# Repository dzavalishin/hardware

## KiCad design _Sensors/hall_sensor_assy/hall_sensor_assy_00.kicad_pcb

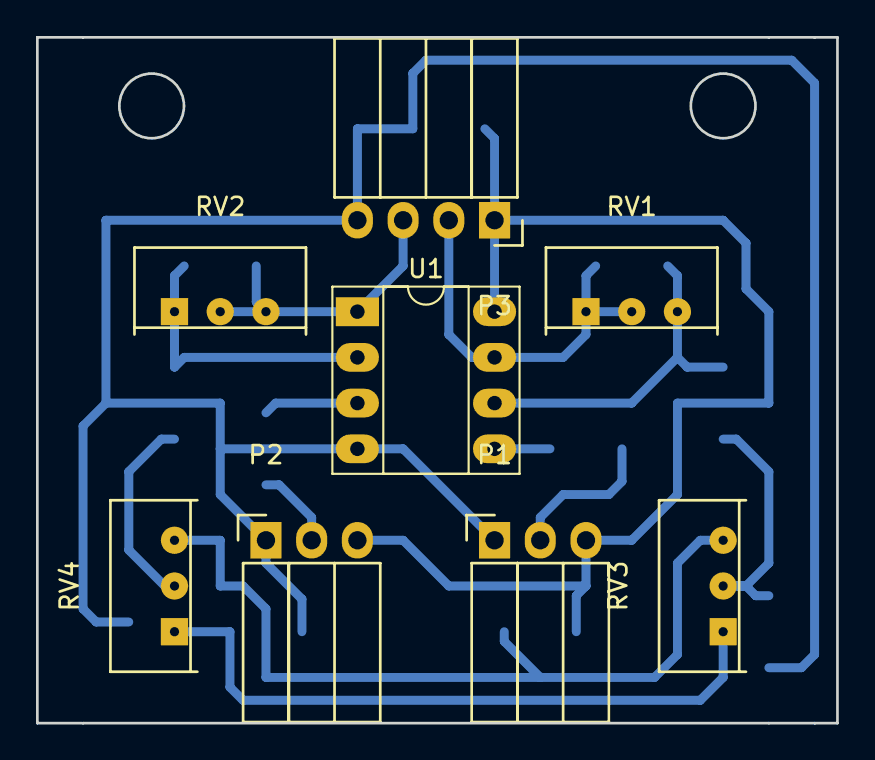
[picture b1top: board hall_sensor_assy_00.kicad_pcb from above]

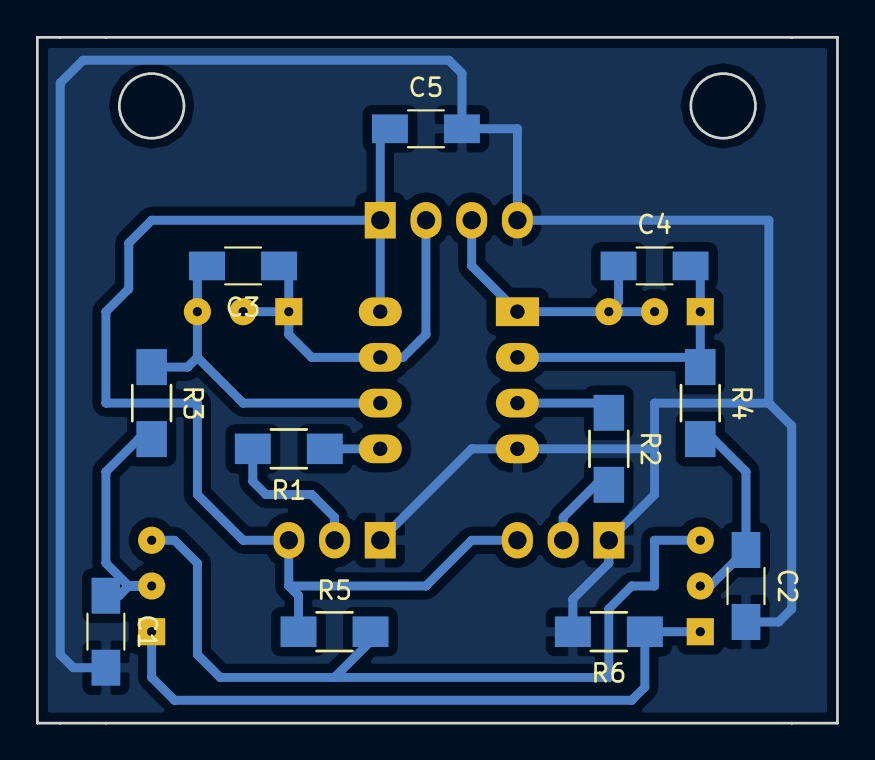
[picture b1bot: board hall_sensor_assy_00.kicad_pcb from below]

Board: 2 copper layers, 44.5 x 38.1 mm, 19 parts (11 on the bottom side), 14 nets.

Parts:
C1, C2, C5: 0,1; C_1206_HandSoldering
C3, C4: 0,01; C_1206_HandSoldering
P1: Hall_L; Socket_Strip_Angled_1x03
P2: Hall_R; Socket_Strip_Angled_1x03
P3: CONN_01X04; Socket_Strip_Angled_1x04
R1, R2: 10k; R_1206_HandSoldering
R3, R4: 22k; R_1206_HandSoldering
R5, R6: 1k; R_1206_HandSoldering
RV1, RV2: 22k; Potentiometer_Trimmer-Suntan-TSR-3386C
RV3, RV4: 2,2k; Potentiometer_Trimmer-Suntan-TSR-3386C
U1: MCP602; DIP-8_W7.62mm_Socket_LongPads

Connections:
+5V: C5.1, P1.3, P2.3, P3.1, R5.1, U1.8
GND: C1.2, C2.2, C5.2, P1.1, P2.1, P3.4, R6.2, U1.4
unnamed: C1.1, R3.2, RV3.2
unnamed: C2.1, R4.2, RV4.2
unnamed: C3.1, P3.2, RV1.1, RV1.2, U1.7
unnamed: C3.2, R3.1, RV1.3, U1.6
unnamed: C4.1, P3.3, RV2.2, RV2.3, U1.1
unnamed: C4.2, R4.1, RV2.1, U1.2
unnamed: P1.2, R1.2
unnamed: P2.2, R2.2
unnamed: R1.1, U1.5
unnamed: R2.1, U1.3
unnamed: R5.2, RV3.3, RV4.3
unnamed: R6.1, RV3.1, RV4.1

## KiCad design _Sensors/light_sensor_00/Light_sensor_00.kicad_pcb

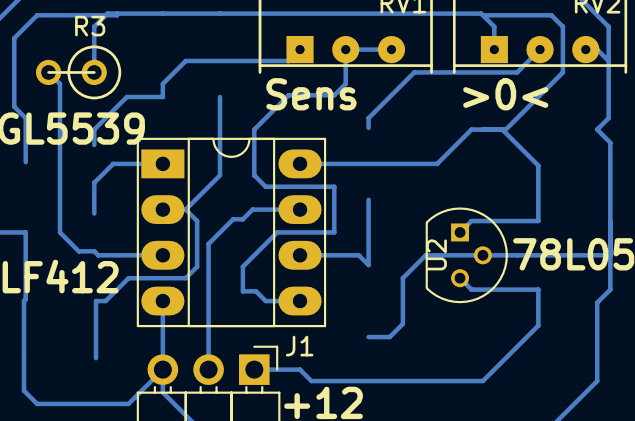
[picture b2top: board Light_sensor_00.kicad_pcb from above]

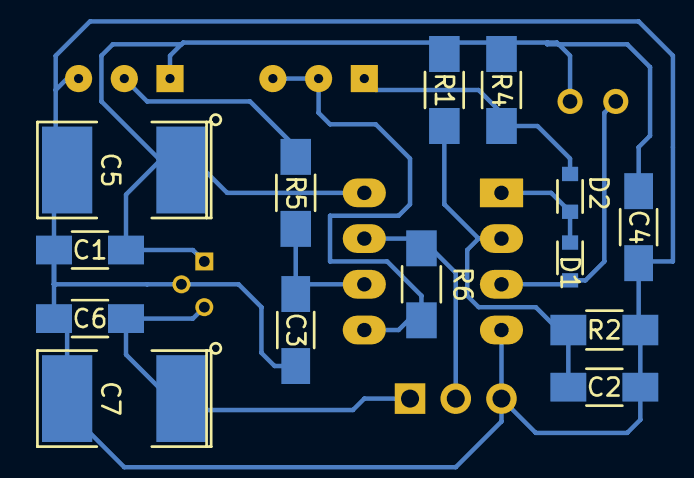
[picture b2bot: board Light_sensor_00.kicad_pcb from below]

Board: 2 copper layers, 20 parts (14 on the bottom side), 11 nets.

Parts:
C1, C2, C3, C4, C6: 0,1; C_1206_HandSoldering
C5: 220,0; SMD-2112_Pol
C7: 47,0; SMD-2112_Pol
D1, D2: 1N4148; D_0805
J1: Pwr/Out; Pin_Header_Angled_1x03_Pitch2.54mm
R1, R2: 220k; R_1206_HandSoldering
R3: GL5539; R1
R4, R5: 1k; R_1206_HandSoldering
R6: 47k; R_1206_HandSoldering
RV1: 10k; Potentiometer_Trimmer-Suntan-TSR-3386C
RV2: 47k; Potentiometer_Trimmer-Suntan-TSR-3386C
U1: LF412CN; DIP-8_W7.62mm_Socket_LongPads
U2: 78L05; TO-92_Molded_Narrow

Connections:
/+5: C1.2, C4.1, C5.1, R1.1, R3.1, R4.1, RV2.1, U1.8, U2.1
/+12: C6.1, C7.1, J1.1, U2.3
/Bal: C3.1, R5.1, U1.6
/Out: J1.2, R6.1, U1.7
/Ref: C2.1, R1.2, R2.1, U1.2
/Sens: D1.2, R3.2, U1.3
GND: C1.1, C2.2, C3.2, C4.2, C5.2, C6.2, C7.2, J1.3, R2.2, RV2.3, U1.4, U2.2
unnamed: D1.1, D2.1, U1.1
unnamed: D2.2, R4.2, RV1.1
unnamed: R5.2, RV2.2
unnamed: R6.2, RV1.2, RV1.3, U1.5

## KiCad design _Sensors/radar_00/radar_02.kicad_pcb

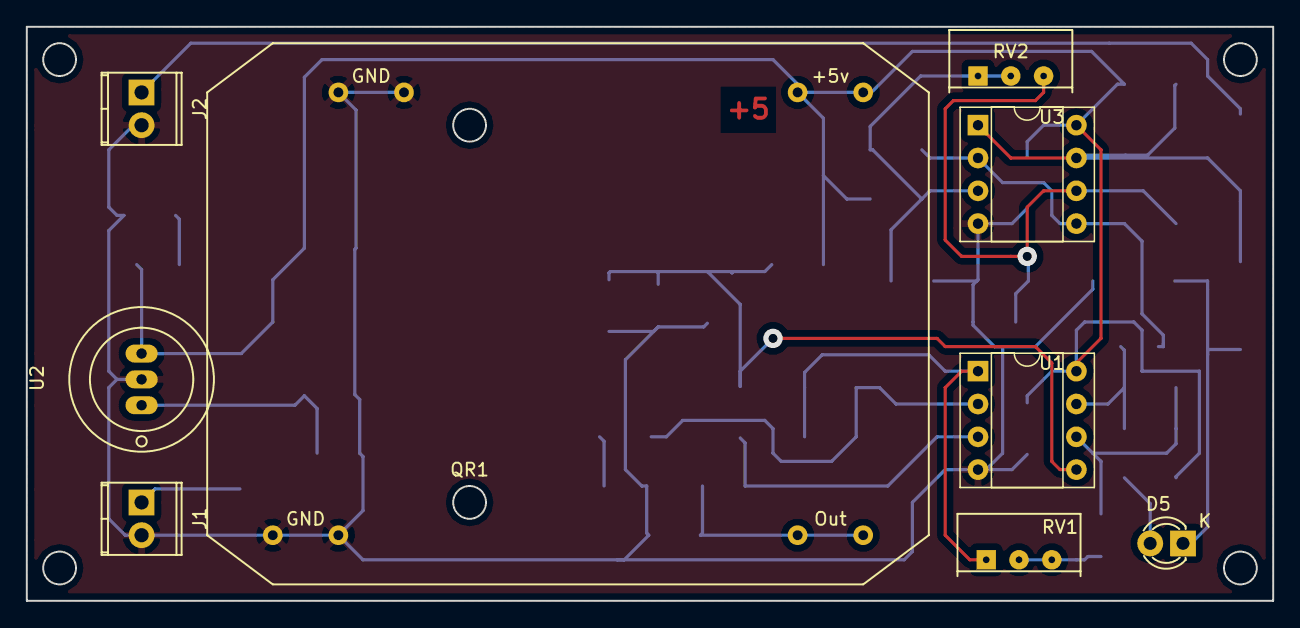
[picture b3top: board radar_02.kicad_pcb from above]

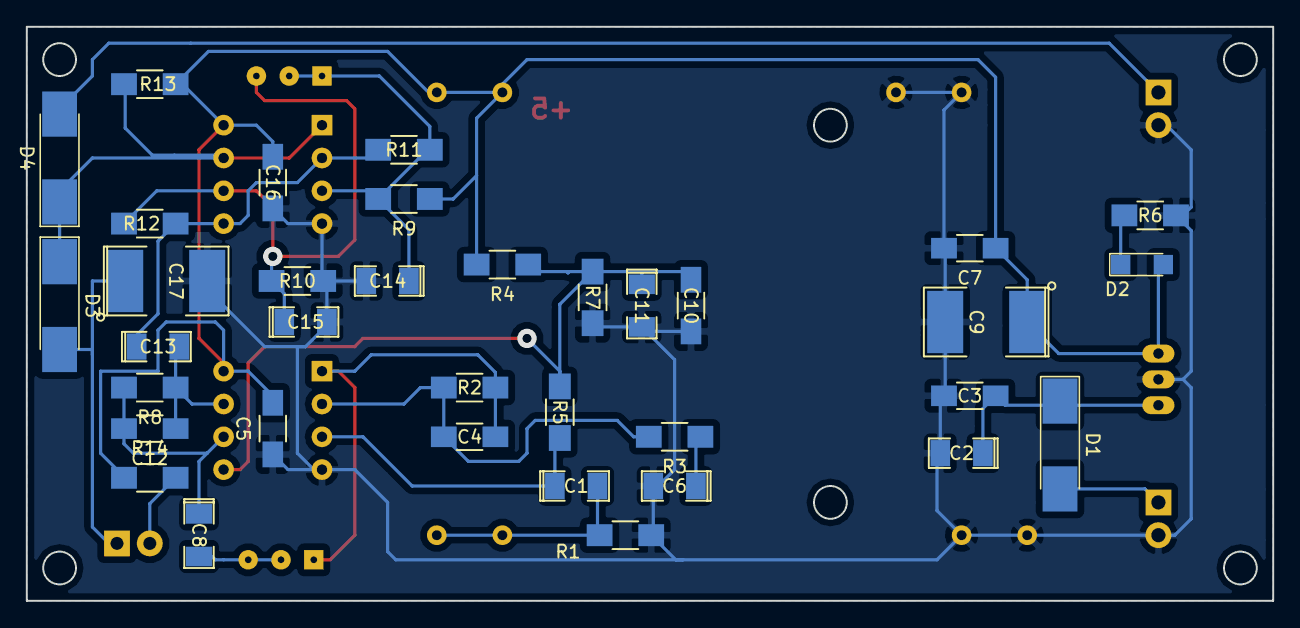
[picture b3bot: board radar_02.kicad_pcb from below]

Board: 2 copper layers, 96.5 x 44.5 mm, 44 parts (35 on the bottom side), 21 nets.

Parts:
C1, C6, C8, C11, C13, C14, C15: 10,0; SMD-1206_Pol
C2: 47,0; SMD-1206_Pol
C3, C5, C7, C10, C16: 0,1; C_1206_HandSoldering
C4, C12: 2200; C_1206_HandSoldering
C9: 220,0; SMD-2112_Pol
C17: 100,0; SMD-2112_Pol
D1, D3, D4: D; D_MELF_Handsoldering
D2: LED; LED_1206
D5: LED; LED-3MM
J1, J2: Screw_Terminal_1x02; TerminalBlock_Pheonix_MPT-2.54mm_2pol
QR1: HB-100-Radar
R1: 13k; R_1206_HandSoldering
R2, R8: 1M; R_1206_HandSoldering
R3: R; R_1206_HandSoldering
R4, R7, R11, R12: 47k; R_1206_HandSoldering
R5: 200k; R_1206_HandSoldering
R6: 2,2k; R_1206_HandSoldering
R9, R10, R13: 4,7k; R_1206_HandSoldering
R14: 1,0k; R_1206_HandSoldering
RV1: 47k; Potentiometer_Trimmer-Suntan-TSR-3386C
RV2: 510; Potentiometer_Trimmer-Suntan-TSR-3386C
U1: LM358; DIP-8_W7.62mm_Socket
U2: 78L05; OldSowjetaera_Transistor_Type-I_BigPads
U3: LM2903; DIP-8_W7.62mm_Socket

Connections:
+5V: C5.2, C7.1, C9.1, C16.2, D2.2, QR1.7, QR1.8, R4.2, R9.1, R13.1, R14.1, U1.8, U2.3, U3.8
GND: C2.2, C3.2, C5.1, C6.2, C7.2, C9.2, C10.1, C11.2, C14.2, C15.2, C16.1, C17.2, J1.2, J2.2, QR1.1, QR1.2, QR1.3, QR1.4, R1.2, R6.1, R7.1, R10.2, U1.4, U2.2, U3.4
unnamed: C1.1, R5.2, U1.3
unnamed: C1.2, QR1.5, QR1.6, R1.1
unnamed: C2.1, C3.1, D1.1, U2.1
unnamed: C4.1, R2.1, RV1.1, U1.1
unnamed: C4.2, R2.2, R3.2, U1.2
unnamed: C6.1, R3.1
unnamed: C8.2, RV1.2, RV1.3
unnamed: C10.2, C11.1, R4.1, R5.1, R7.2, U1.5
unnamed: C12.1, C13.2, R8.1, U1.7
unnamed: C8.1, C12.2, R8.2, U1.6
unnamed: C13.1, R11.1, R12.1, U3.2, U3.5
unnamed: C14.1, R9.2, R11.2, RV2.1, RV2.2, U3.3
unnamed: C15.1, R10.1, R12.2, RV2.3, U3.6
unnamed: C17.1, D3.2, D5.1
unnamed: D1.2, J1.1
unnamed: D2.1, R6.2
unnamed: D3.1, D4.1, R13.2, U3.1, U3.7
unnamed: D4.2, J2.1
unnamed: D5.2, R14.2
